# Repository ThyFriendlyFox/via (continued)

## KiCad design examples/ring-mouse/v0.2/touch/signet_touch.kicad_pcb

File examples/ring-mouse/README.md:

# Signet — prototype series

A mouse you wear as a ring. Six small boards sit on the faces of a hexagonal ring round the index
finger, soldered edge to edge. The ring turns with the hand and moves the cursor; the thumb slides
along a strip to scroll and presses the ring's side to click. It talks Bluetooth LE to the computer
as an ordinary mouse.

This folder is a project made with the EE Workcenter, kept the way
[Last Hit](https://github.com/ThyFriendlyFox/vape-prototype) keeps its prototypes: each version is
its own folder, each tile in it a whole KiCad project built from its `design.py`, with its README,
its pictures under `docs/` and its firmware. The versions came from a loop: each pass judged the
last version against a checklist and made the next ([`LOOP.md`](LOOP.md)).

The latest version, [v0.4](v0.4/), turning:

| The thumb's side | Along the finger |
|---|---|
|  |  |

## Versions

| Version | Ring | What changed | Firmware | Commit |
|---|---|---|---|---|
| [v0.1](v0.1/) | 6 tiles round a 20 mm cylinder, 12 mm along the finger; the radio tile 15.6 mm wide, 4 layers; touch 4 layers; the others 10.8 mm, 2 layers | the first ring: a BLE module, an IMU, a 3-channel scroll strip, 2 clicks, a charger, a 3.3 V rail and a 20 mAh cell on 6 tiles joined by 8-pad solder joints | the scroll strip's decoder, 8 host tests | `e4181fa` |
| [v0.2](v0.2/) | as v0.1; every tile 4 layers | the first pass of the loop: ground only inside, so every face is black; solder in every joint and a foil cell in the pictures; L and R on the clicks, the name on the motion tile | the air mouse: the gyro turned back from the motion tile's angle into cursor counts, with the strip as a clutch, 7 host tests | `254e0bb` |
| [v0.3](v0.3/) | as v0.2; the joint pads 0.8 mm along the edge | the second pass: the light moves from under the thumb to the motion tile, by the name; a TVS diode guards the charging pads; 0.5 mm of mask between the joint pads; smaller solder beads in the pictures | as v0.2 | `07a3ccb` |
| [v0.4](v0.4/) (current) | 6 tiles whose neighbours share each inner corner: radio 15.6 mm, touch and motion 12.18 mm, clicks and power 9.79 mm, cell 10.82 mm | the third pass: the ring closes at the radio's 2 joints, which stood 1.3 mm open; the assembly at its measured heights | the air mouse at the motion tile's new angle, -75.90 degrees | in work |

Before v0.1, 2 flat boards were tried: the face of a signet ring, then a ring-shaped PCB with a
finger hole and a crown. Neither wrapped the finger, and the owner asked for the circuit on the
surface of the cylinder. They have no folder.

## Working on the ring

Run from a version's folder; each tile is a nested project.

```sh
python3 footprints/make_footprints.py           # the joint and the scroll strip, into footprints/Ring.pretty
workcenter design radio/design.py --route       # one tile's KiCad project, routed; likewise each tile
workcenter gates radio --strict                 # ERC, DRC, simulation, export; GREEN means done
make -C firmware test                           # the firmware's host tests
workcenter pictures .                           # every tile's renders and GIF, and the assembly (assembly.py)
```

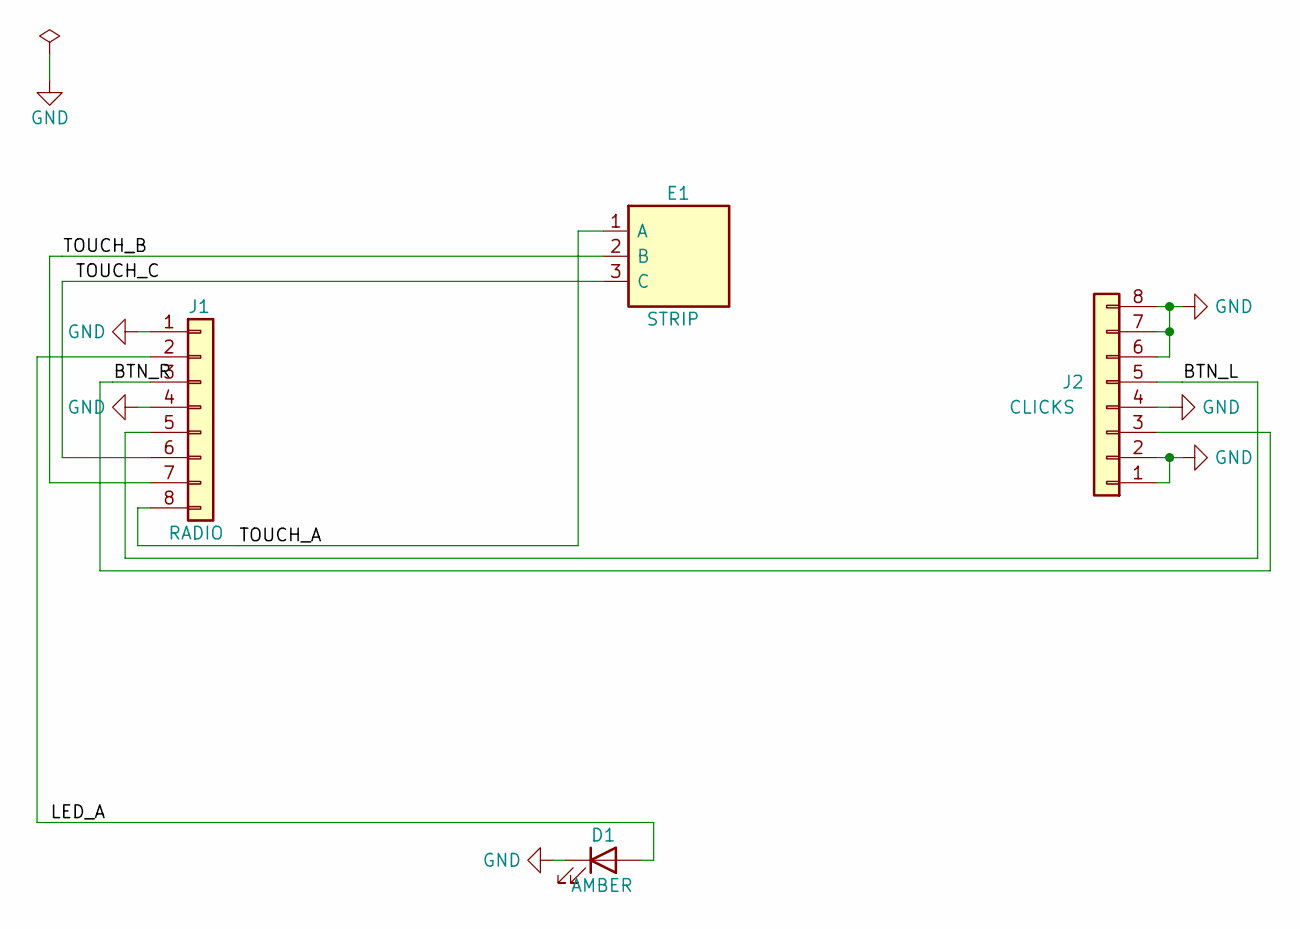
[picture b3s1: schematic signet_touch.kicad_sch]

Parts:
D1: AMBER; LED_0402_1005Metric
E1: STRIP; TouchStrip_3ch_6x
J1: RADIO; Joint_Edge_1x08_P1.3mm
J2: CLICKS; Joint_Edge_1x08_P1.3mm

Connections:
/BTN_L: J1.5, J2.5
/BTN_R: J1.3, J2.3
/LED_A: D1.2 (A), J1.2
/TOUCH_A: E1.1 (A), J1.8
/TOUCH_B: E1.2 (B), J1.7
/TOUCH_C: E1.3 (C), J1.6
GND: D1.1 (K), J1.1, J1.4, J2.1, J2.2, J2.4, J2.6, J2.7, J2.8

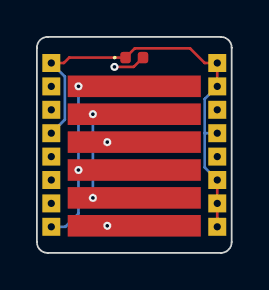
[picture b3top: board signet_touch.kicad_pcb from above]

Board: 4 copper layers, 10.8 x 12.0 mm, 4 parts (0 on the bottom side), 7 nets.

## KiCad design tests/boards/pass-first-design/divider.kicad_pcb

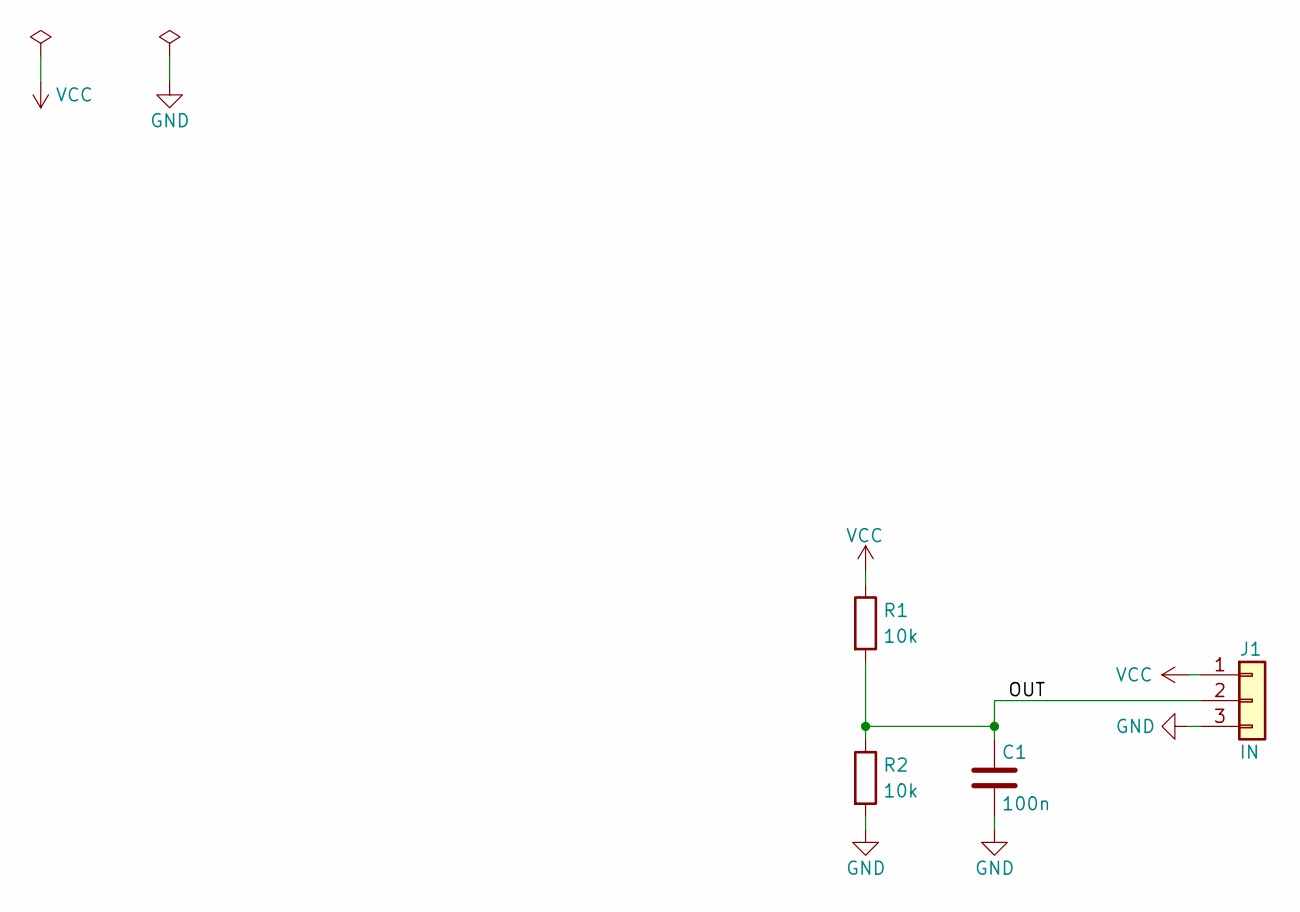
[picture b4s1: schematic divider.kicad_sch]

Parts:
C1: 100n; C_0603_1608Metric
J1: IN; PinHeader_1x03_P2.54mm_Vertical
R1, R2: 10k; R_0603_1608Metric

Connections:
/OUT: C1.1, J1.2, R1.2, R2.1
GND: C1.2, J1.3, R2.2
VCC: J1.1, R1.1

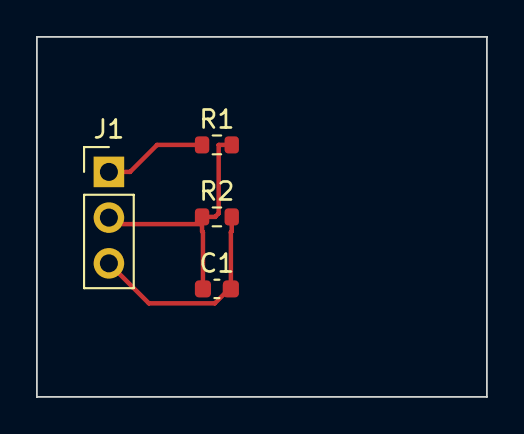
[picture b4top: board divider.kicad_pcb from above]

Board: 2 copper layers, 25.0 x 20.0 mm, 4 parts (0 on the bottom side), 3 nets.

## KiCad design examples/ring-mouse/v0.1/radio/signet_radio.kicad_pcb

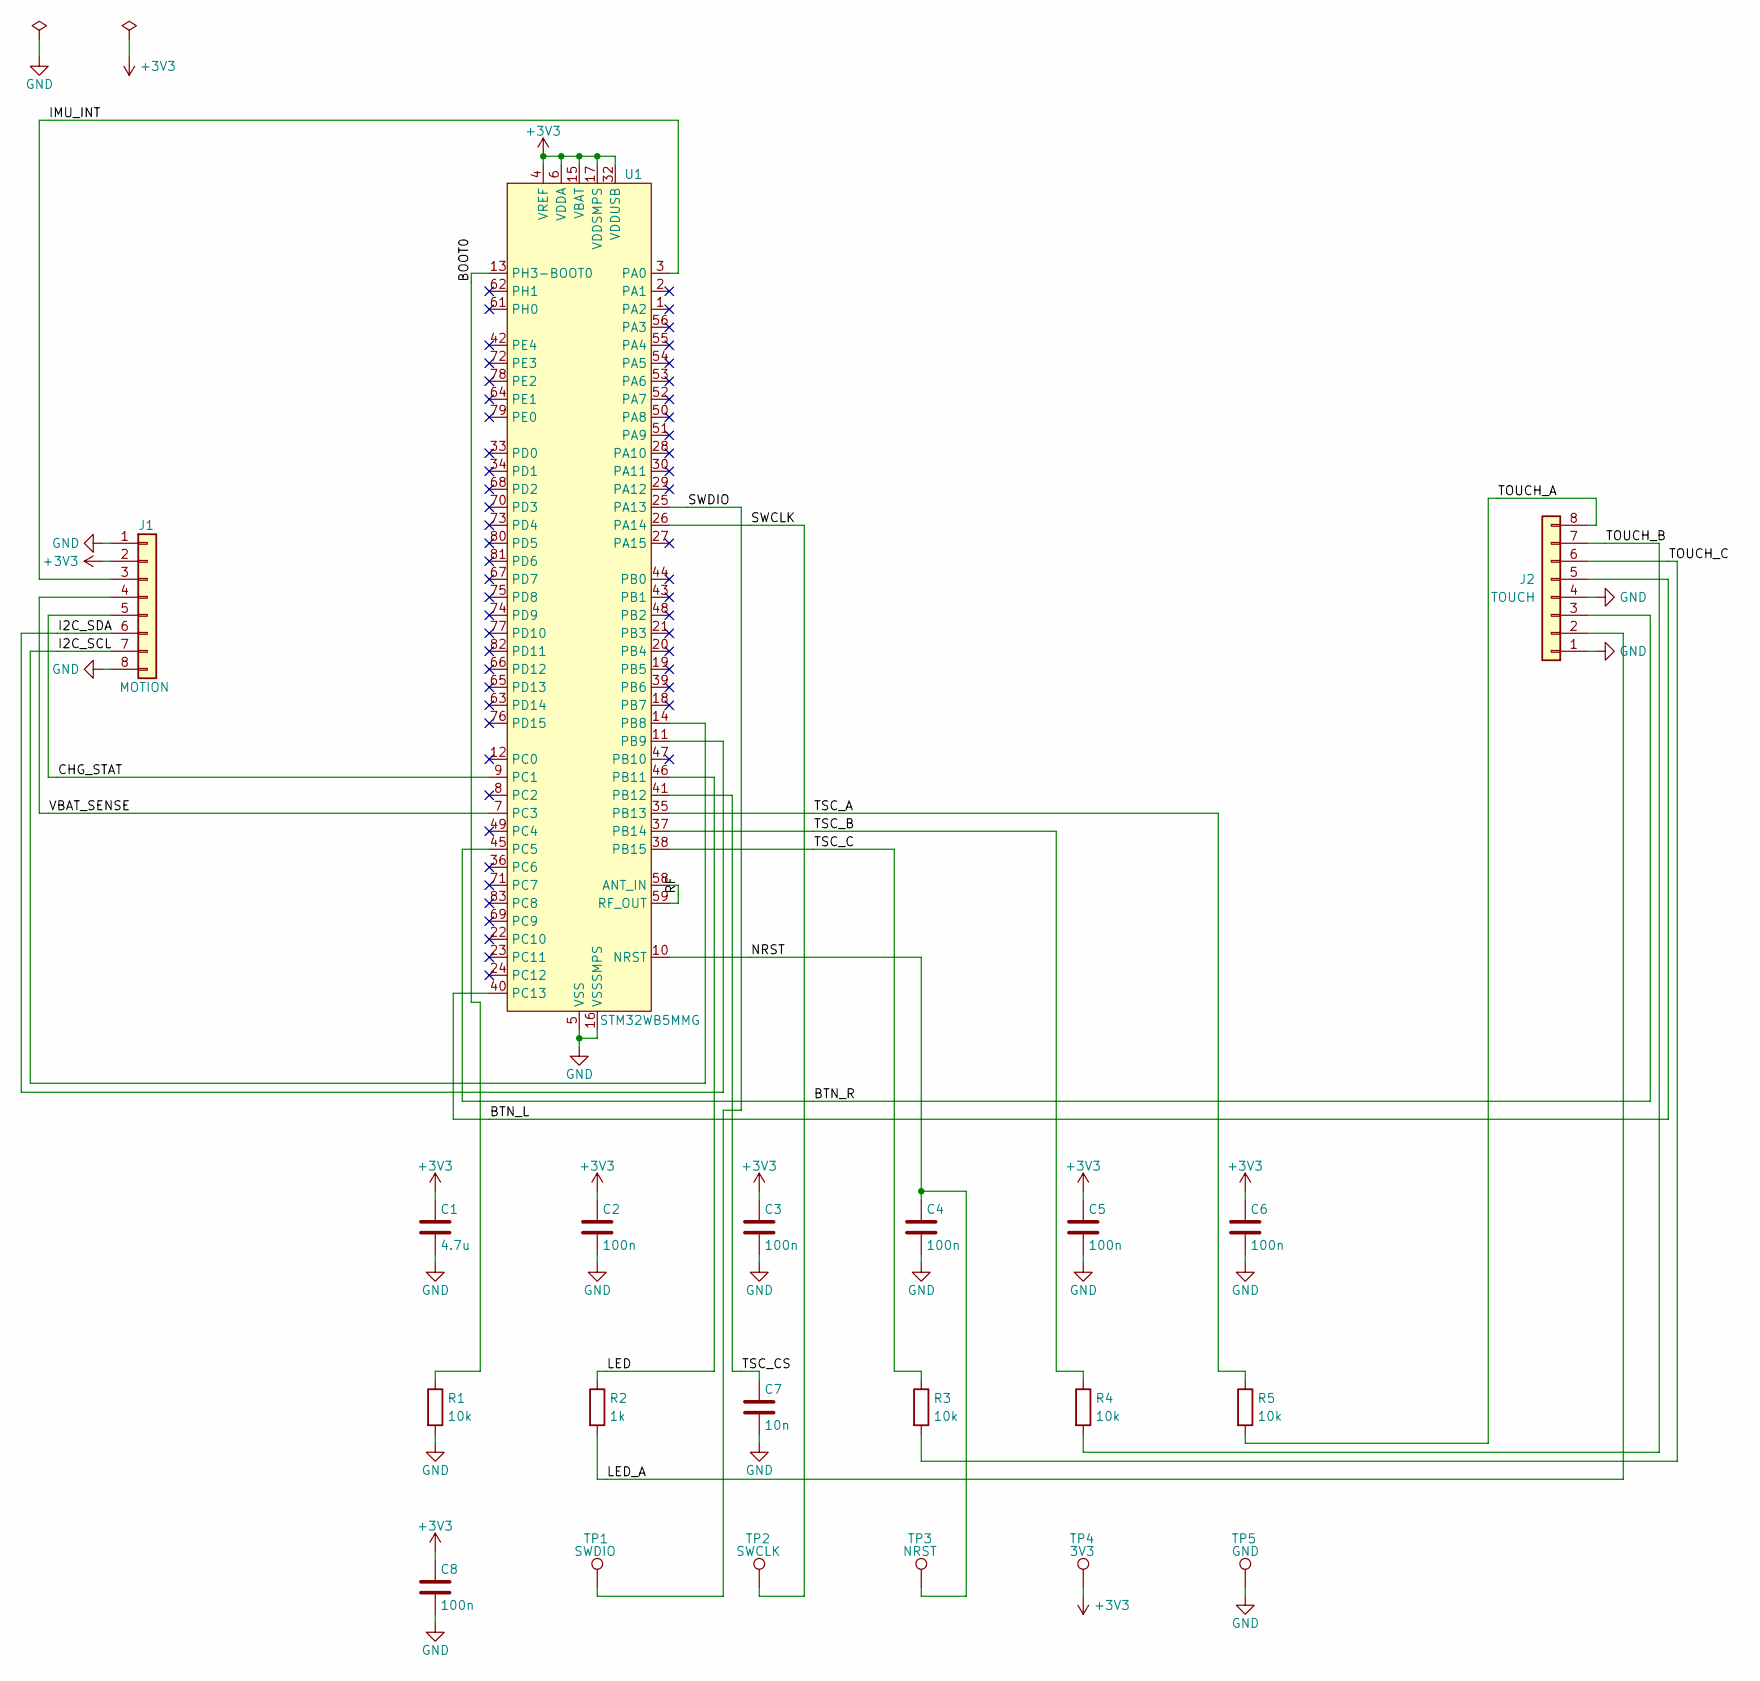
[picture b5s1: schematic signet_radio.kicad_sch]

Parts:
C1: 4.7u; C_0402_1005Metric
C2, C3, C4, C5, C6, C8: 100n; C_0402_1005Metric
C7: 10n; C_0402_1005Metric
J1: MOTION; Joint_Edge_1x08_P1.3mm
J2: TOUCH; Joint_Edge_1x08_P1.3mm
R1, R3, R4, R5: 10k; R_0402_1005Metric
R2: 1k; R_0402_1005Metric
TP1: SWDIO; TestPoint_Pad_D1.0mm
TP2: SWCLK; TestPoint_Pad_D1.0mm
TP3: NRST; TestPoint_Pad_D1.0mm
TP4: 3V3; TestPoint_Pad_D1.0mm
TP5: GND; TestPoint_Pad_D1.0mm
U1: STM32WB5MMG; ST-SiP-LGA-86-11x7.3mm

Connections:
+3V3: C1.1, C2.1, C3.1, C5.1, C6.1, C8.1, J1.2, TP4.1, U1.4 (VREF), U1.6 (VDDA), U1.15 (VBAT), U1.17 (VDDSMPS), U1.32 (VDDUSB)
/BOOT0: R1.1, U1.13 (PH3-BOOT0)
/BTN_L: J2.5, U1.40 (PC13)
/BTN_R: J2.3, U1.45 (PC5)
/CHG_STAT: J1.5, U1.9 (PC1)
/I2C_SCL: J1.7, U1.14 (PB8)
/I2C_SDA: J1.6, U1.11 (PB9)
/IMU_INT: J1.3, U1.3 (PA0)
/LED: R2.1, U1.46 (PB11)
/LED_A: J2.2, R2.2
/NRST: C4.1, TP3.1, U1.10 (NRST)
/RF: U1.58 (ANT_IN), U1.59 (RF_OUT)
/SWCLK: TP2.1, U1.26 (PA14)
/SWDIO: TP1.1, U1.25 (PA13)
/TOUCH_A: J2.8, R5.2
/TOUCH_B: J2.7, R4.2
/TOUCH_C: J2.6, R3.2
/TSC_A: R5.1, U1.35 (PB13)
/TSC_B: R4.1, U1.37 (PB14)
/TSC_C: R3.1, U1.38 (PB15)
/TSC_CS: C7.1, U1.41 (PB12)
/VBAT_SENSE: J1.4, U1.7 (PC3)
GND: C1.2, C2.2, C3.2, C4.2, C5.2, C6.2, C7.2, C8.2, J1.1, J1.8, J2.1, J2.4, R1.2, TP5.1, U1.5 (VSS), U1.16 (VSSSMPS), U1.31 (VSS), U1.57 (VSS), U1.60 (VSS), U1.84 (VSS), U1.86 (VSS)

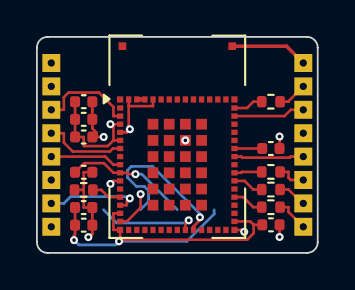
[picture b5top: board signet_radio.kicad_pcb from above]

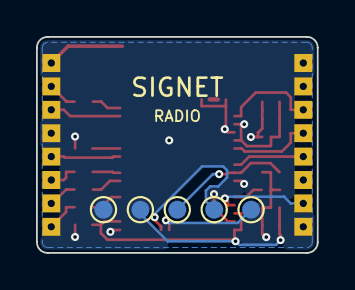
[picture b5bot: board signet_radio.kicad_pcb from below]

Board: 4 copper layers, 15.6 x 12.0 mm, 21 parts (5 on the bottom side), 23 nets.

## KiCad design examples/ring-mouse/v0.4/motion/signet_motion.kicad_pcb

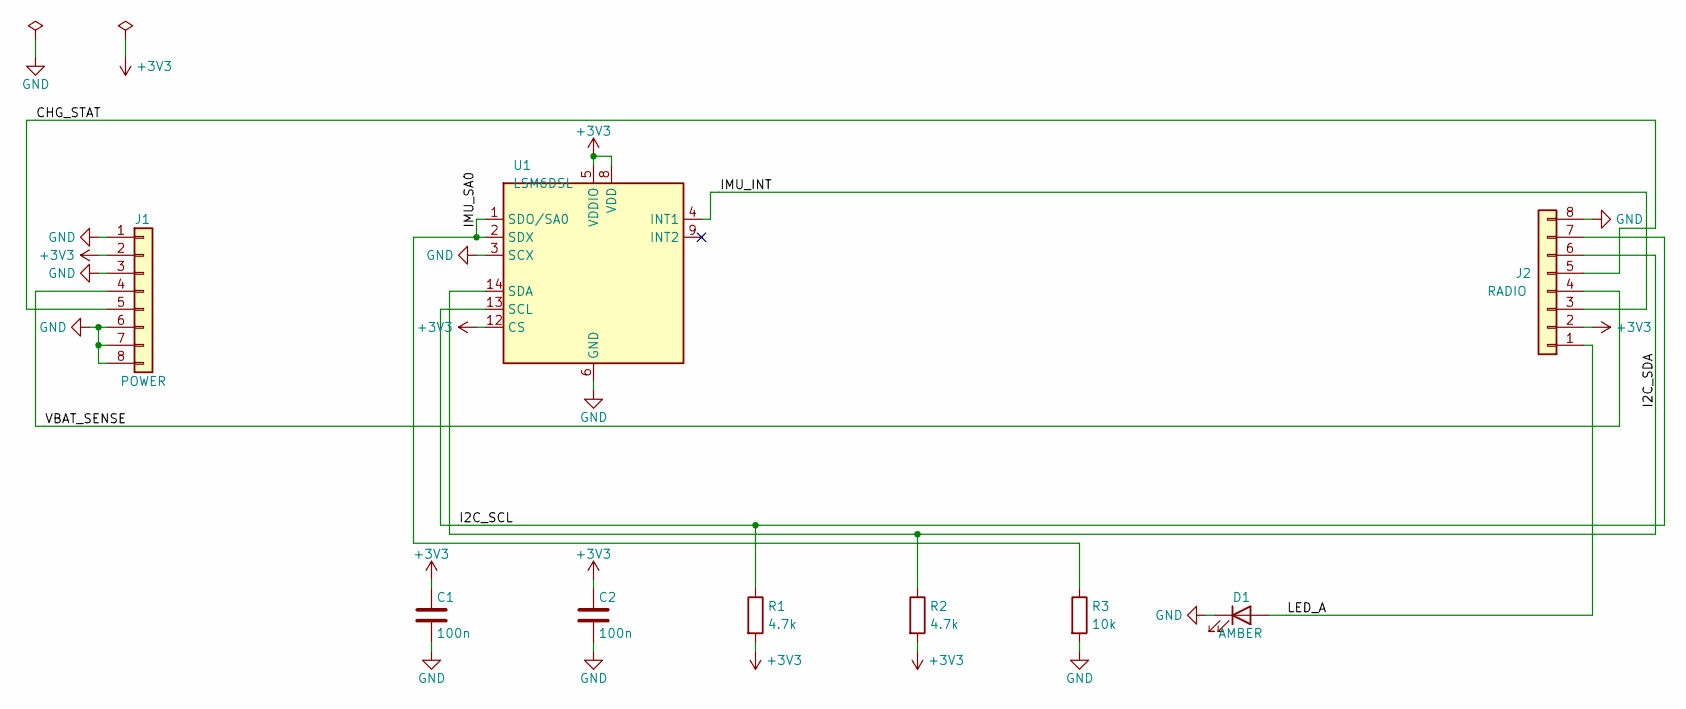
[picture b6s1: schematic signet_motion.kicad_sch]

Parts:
C1, C2: 100n; C_0402_1005Metric
D1: AMBER; LED_0402_1005Metric
J1: POWER; Joint_Edge_1x08_P1.3mm
J2: RADIO; Joint_Edge_1x08_P1.3mm
R1, R2: 4.7k; R_0402_1005Metric
R3: 10k; R_0402_1005Metric
U1: LSM6DSL; LGA-14_3x2.5mm_P0.5mm_LayoutBorder3x4y

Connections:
+3V3: C1.1, C2.1, J1.2, J2.2, R1.2, R2.2, U1.5 (VDDIO), U1.8 (VDD), U1.12 (CS)
/CHG_STAT: J1.5, J2.5
/I2C_SCL: J2.7, R1.1, U1.13 (SCL)
/I2C_SDA: J2.6, R2.1, U1.14 (SDA)
/IMU_INT: J2.3, U1.4 (INT1)
/IMU_SA0: R3.1, U1.1 (SDO/SA0), U1.2 (SDX)
/LED_A: D1.2 (A), J2.1
/VBAT_SENSE: J1.4, J2.4
GND: C1.2, C2.2, D1.1 (K), J1.1, J1.3, J1.6, J1.7, J1.8, J2.8, R3.2, U1.3 (SCX), U1.6 (GND), U1.7 (GND)

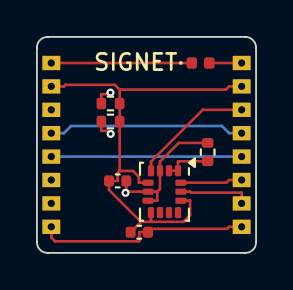
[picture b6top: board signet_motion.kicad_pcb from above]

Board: 4 copper layers, 12.2 x 12.0 mm, 9 parts (0 on the bottom side), 9 nets.

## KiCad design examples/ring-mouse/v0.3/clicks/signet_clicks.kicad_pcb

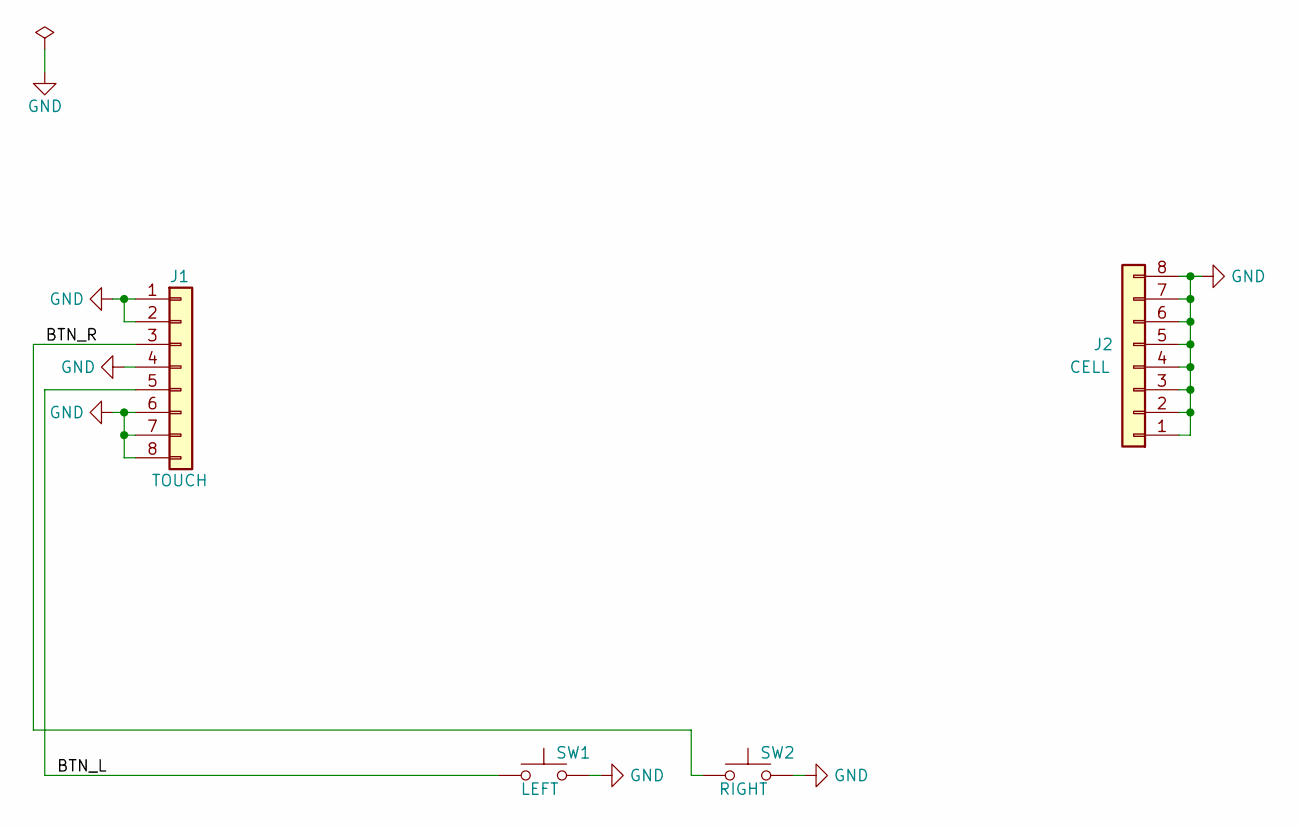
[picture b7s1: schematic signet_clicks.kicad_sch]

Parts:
J1: TOUCH; Joint_Edge_1x08_P1.3mm
J2: CELL; Joint_Edge_1x08_P1.3mm
SW1: LEFT; SW_Push_1P1T_NO_CK_KMR2
SW2: RIGHT; SW_Push_1P1T_NO_CK_KMR2

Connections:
/BTN_L: J1.5, SW1.1
/BTN_R: J1.3, SW2.1
GND: J1.1, J1.2, J1.4, J1.6, J1.7, J1.8, J2.1, J2.2, J2.3, J2.4, J2.5, J2.6, J2.7, J2.8, SW1.2, SW2.2

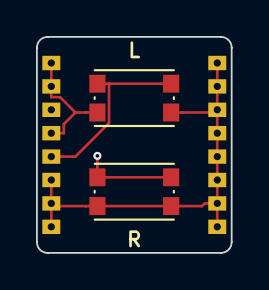
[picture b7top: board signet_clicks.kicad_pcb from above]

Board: 4 copper layers, 10.8 x 12.0 mm, 4 parts (0 on the bottom side), 3 nets.
